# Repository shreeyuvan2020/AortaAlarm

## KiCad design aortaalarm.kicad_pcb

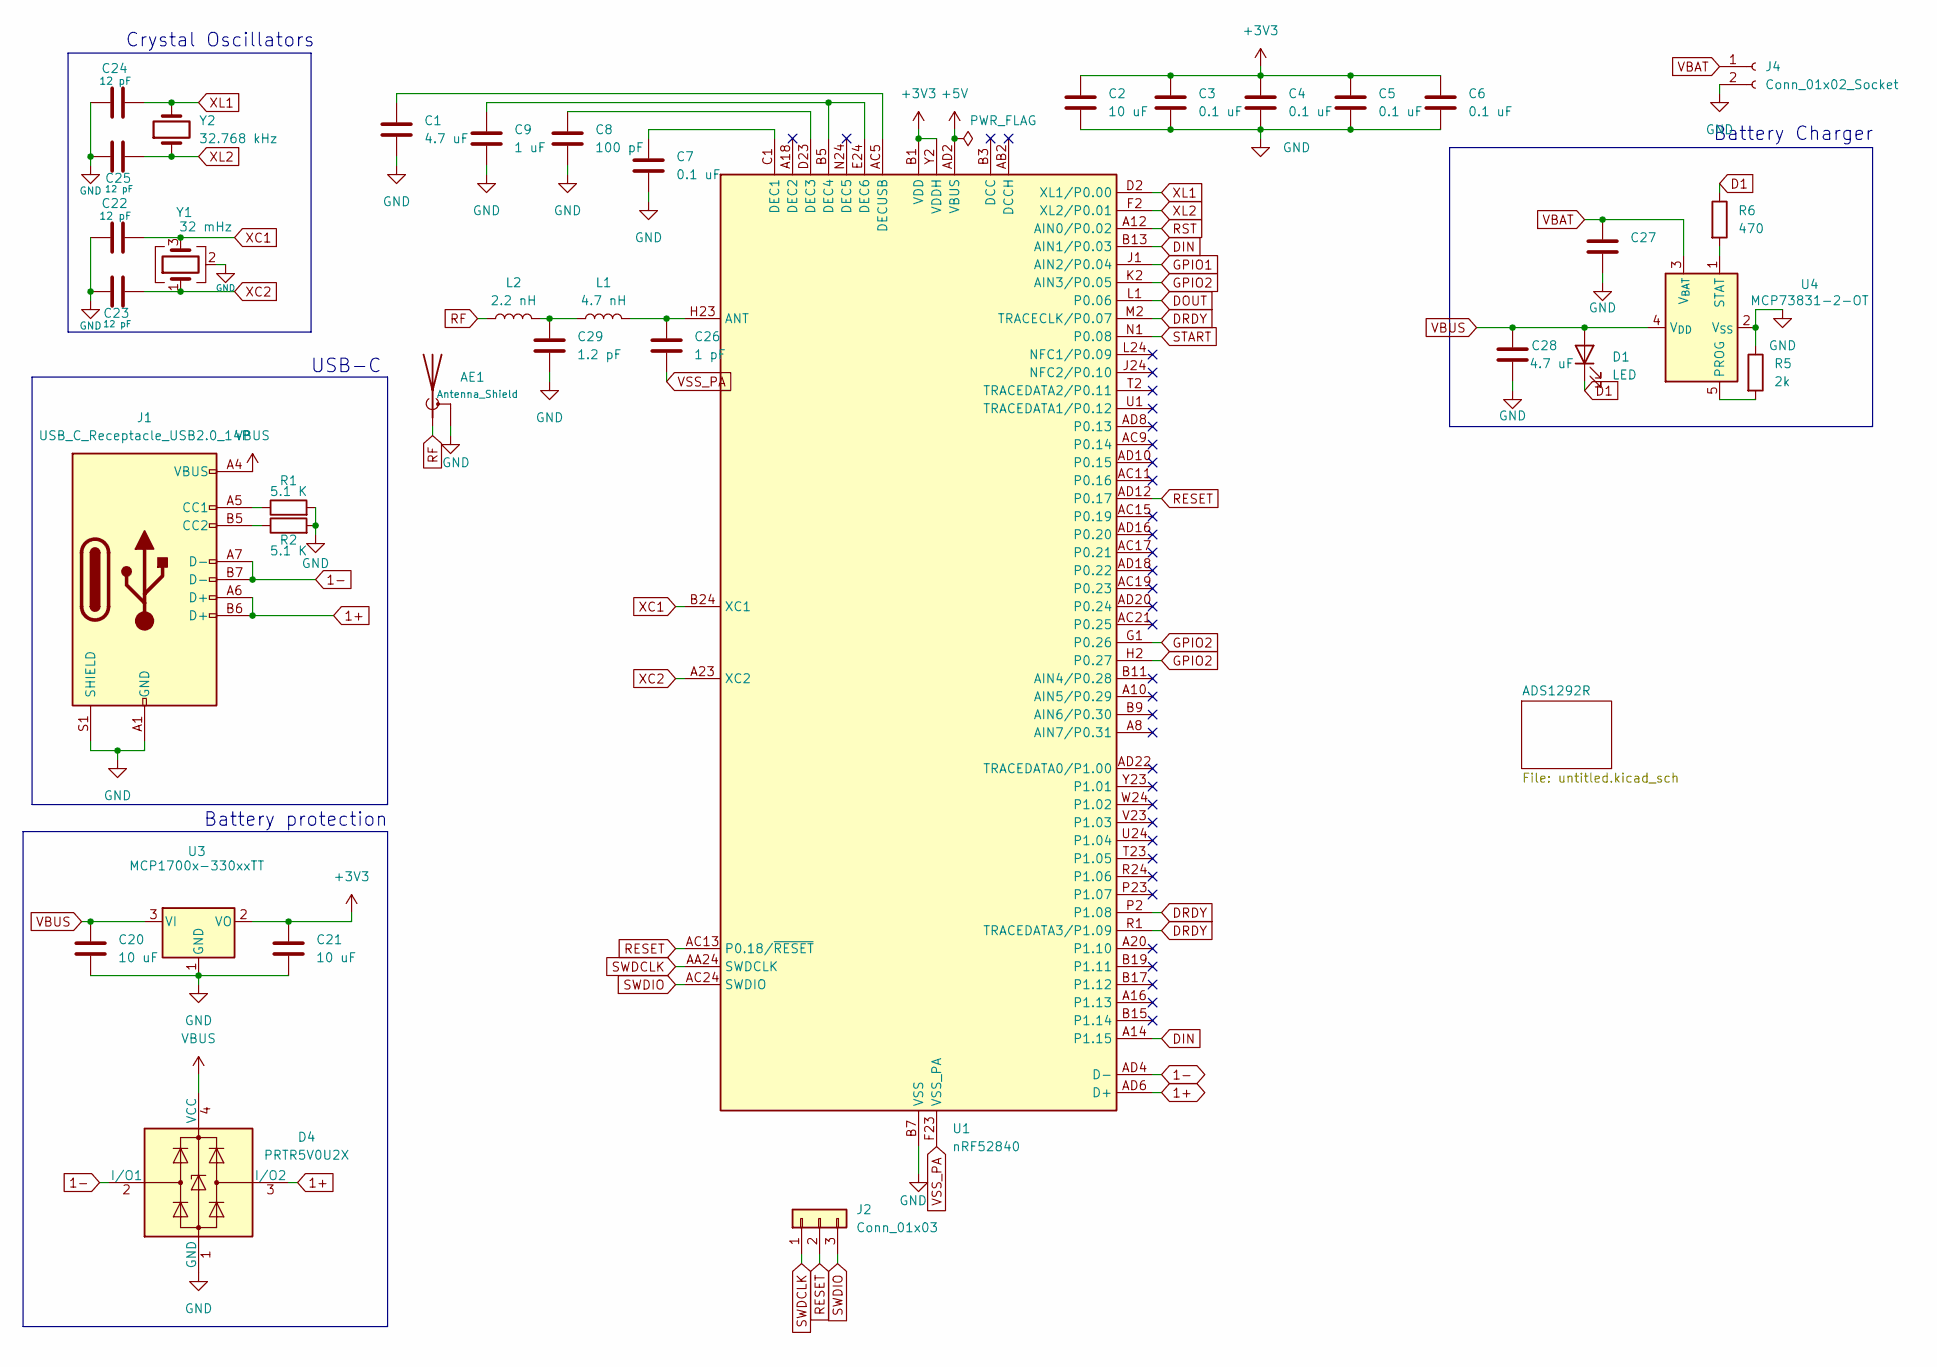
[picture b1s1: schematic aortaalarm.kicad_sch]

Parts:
AE1: Antenna_Shield; Texas_SWRA117D_2.4GHz_Right
C1, C27, C28: 4.7 uF; C_0603_1608Metric
C2, C20, C21: 10 uF; C_0603_1608Metric
C3, C4, C5, C6, C7: 0.1 uF; C_0402_1005Metric
C8: 100 pF; C_0402_1005Metric
C9: 1 uF; C_0402_1005Metric
C22, C23, C24, C25: 12 pF; C_0402_1005Metric
C26: 1 pF; C_0402_1005Metric
C29: 1.2 pF; C_0402_1005Metric
D1: LED; D_0805_2012Metric
D4: PRTR5V0U2X; SOT-143
J1: USB_C_Receptacle_USB2.0_14P; USB_C_Receptacle_HRO_TYPE-C-31-M-12
J2: Conn_01x03; PinHeader_1x03_P2.54mm_Vertical
J4: Conn_01x02_Socket; JST_PH_S2B-PH-K_1x02_P2.00mm_Horizontal
L1: 4.7 nH; L_0402_1005Metric
L2: 2.2 nH; L_0402_1005Metric
R1, R2: 5.1 K; R_0603_1608Metric
R5: 2k; R_0603_1608Metric
R6: 470; R_0603_1608Metric
U1: nRF52840; Nordic_AQFN-73-1EP_7x7mm_P0.5mm
U3: MCP1700x-330xxTT; SOT-23
U4: MCP73831-2-OT; SON50P200X300X100-9N
Y1: 32 mHz; Crystal_SMD_3225-4Pin_3.2x2.5mm
Y2: 32.768 kHz; Crystal_SMD_3215-2Pin_3.2x1.5mm

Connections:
1+: D4.3 (I/O2), J1.A6 (D+), J1.B6 (D+), U1.AD6 (D+)
1-: D4.2 (I/O1), J1.A7 (D-), J1.B7 (D-), U1.AD4 (D-)
+3V3: C2.1, C3.1, C4.1, C5.1, C6.1, C21.1, U1.A22 (VDD), U1.AD14 (VDD), U1.AD23 (VDD), U1.B1 (VDD), U1.W1 (VDD), U1.Y2 (VDDH), U3.2 (VO); also elsewhere on the board
+5V: U1.AD2 (VBUS)
D1: D1.1 (K), R6.1
DIN: U1.A14 (P1.15), U1.B13 (AIN1/P0.03); also elsewhere on the board
DOUT: U1.L1 (P0.06); also elsewhere on the board
DRDY: U1.M2 (TRACECLK/P0.07), U1.P2 (P1.08), U1.R1 (TRACEDATA3/P1.09); also elsewhere on the board
GND: AE1.2 (Shield), C1.2, C2.2, C3.2, C4.2, C5.2, C6.2, C7.2, C8.2, C9.2, C20.2, C21.2, C22.1, C23.1, C24.1, C25.1, C27.2, C28.2, C29.2, D4.1 (GND), J1.A1 (GND), J1.A12 (GND), J1.B1 (GND), J1.B12 (GND), J1.S1 (SHIELD), J4.2, R1.2, R2.2, R5.1, U1.B7 (VSS), U1.EP (VSS), U3.1 (GND), U4.2 (V_{SS}), Y1.2 (G), Y1.4 (G); also elsewhere on the board
GPIO1: U1.J1 (AIN2/P0.04); also elsewhere on the board
GPIO2: U1.G1 (P0.26), U1.H2 (P0.27), U1.K2 (AIN3/P0.05); also elsewhere on the board
unnamed: C29.1, L1.1, L2.2
unnamed: J1.A5 (CC1), R1.1
unnamed: J1.B5 (CC2), R2.1
unnamed: C26.1, L1.2, U1.H23 (ANT)
unnamed: C7.1, U1.C1 (DEC1)
unnamed: C8.1, U1.D23 (DEC3)
unnamed: C9.1, U1.B5 (DEC4), U1.E24 (DEC6)
unnamed: C1.1, U1.AC5 (DECUSB)
unnamed: R5.2, U4.5 (PROG)
unnamed: R6.2, U4.1 (STAT)
RESET: J2.2, U1.AC13 (P0.18/~RESET), U1.AD12 (P0.17)
RF: AE1.1 (A), L2.1
RST: U1.A12 (AIN0/P0.02); also elsewhere on the board
START: U1.N1 (P0.08); also elsewhere on the board
SWDCLK: J2.1, U1.AA24 (SWDCLK); also elsewhere on the board
SWDIO: J2.3, U1.AC24 (SWDIO)
VBAT: C27.1, J4.1, U4.3 (V_{BAT})
VBUS: C20.1, C28.1, D1.2 (A), D4.4 (VCC), J1.A4 (VBUS), J1.A9 (VBUS), J1.B4 (VBUS), J1.B9 (VBUS), U3.3 (VI), U4.4 (V_{DD})
VSS_PA: C26.2, U1.F23 (VSS_PA)
XC1: C22.2, U1.B24 (XC1), Y1.3
XC2: C23.2, U1.A23 (XC2), Y1.1
XL1: C24.2, U1.D2 (XL1/P0.00), Y2.2
XL2: C25.2, U1.F2 (XL2/P0.01), Y2.1

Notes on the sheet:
Battery protection
USB-C
Crystal Oscillators
Battery Charger

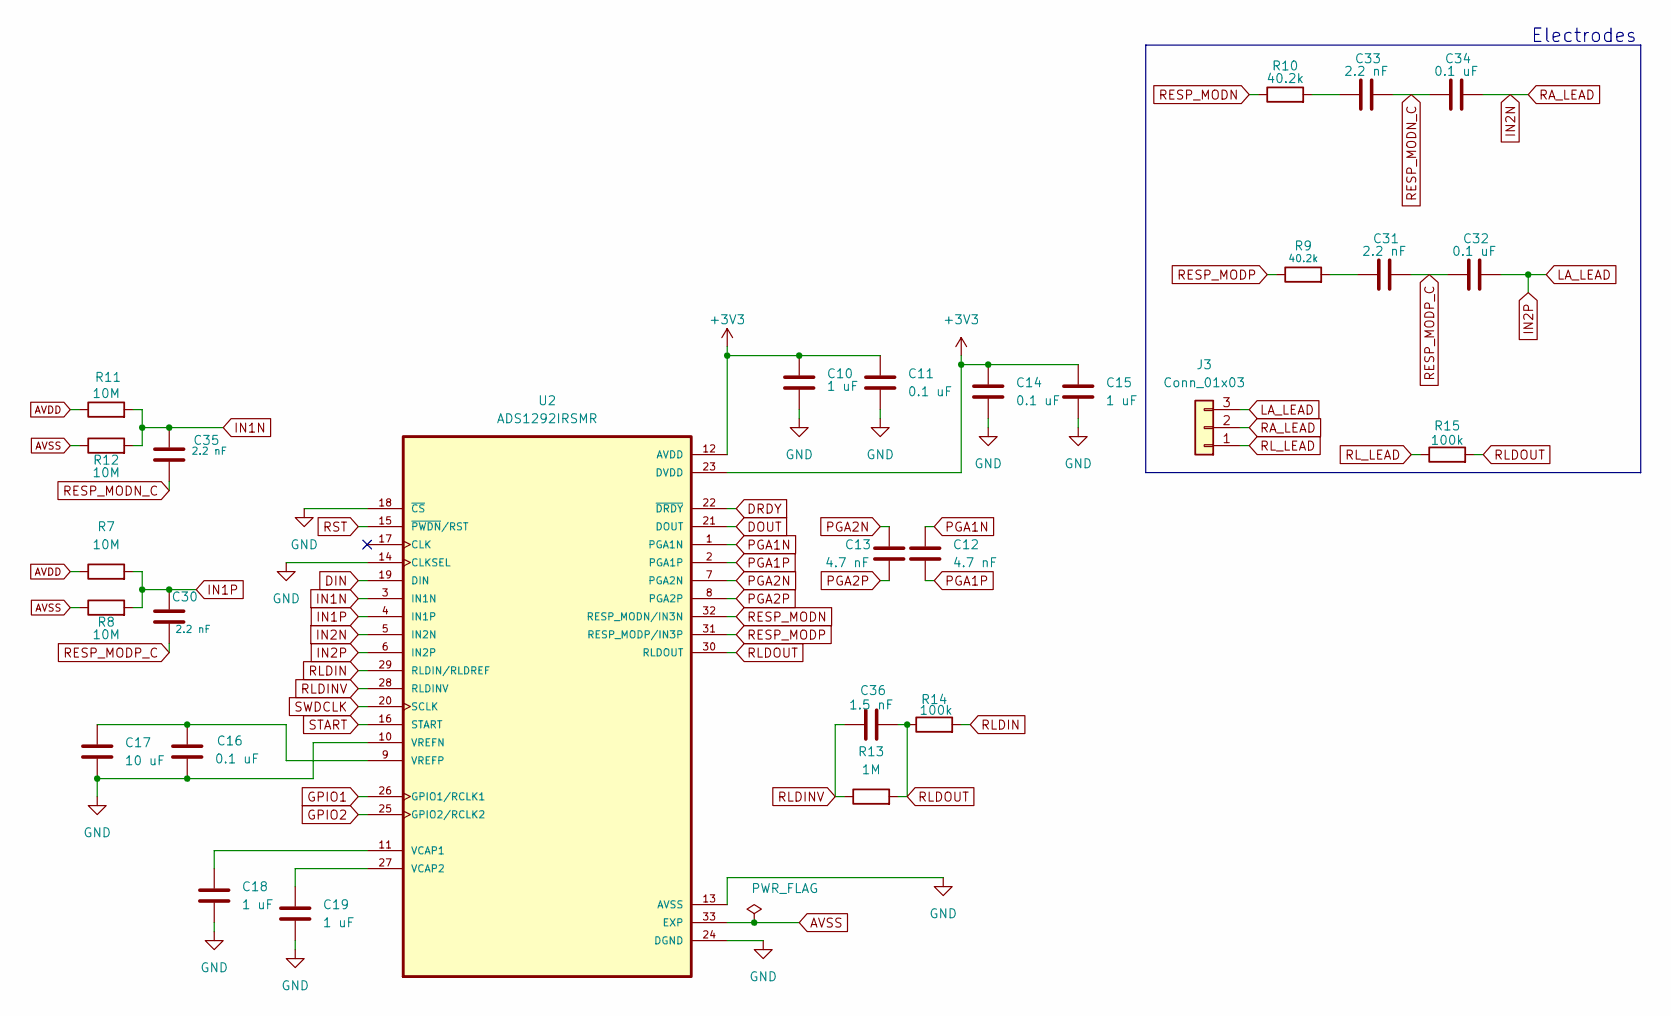
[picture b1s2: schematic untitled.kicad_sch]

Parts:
C10, C15, C18, C19: 1 uF; C_0402_1005Metric
C11, C14, C16, C32, C34: 0.1 uF; C_0402_1005Metric
C12, C13: 4.7 nF; C_0402_1005Metric
C17: 10 uF; C_0603_1608Metric
C30, C31, C33, C35: 2.2 nF; C_0402_1005Metric
C36: 1.5 nF; C_0402_1005Metric
J3: Conn_01x03; PinSocket_1x03_P2.54mm_Vertical
R7, R8, R11, R12: 10M; R_0603_1608Metric
R9, R10: 40.2k; R_0603_1608Metric
R13: 1M; R_0603_1608Metric
R14, R15: 100k; R_0603_1608Metric
U2: ADS1292IRSMR; QFN40P400X400X100-33N

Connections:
+3V3: C10.1, C11.1, C14.1, C15.1, U2.12 (AVDD), U2.23 (DVDD); also elsewhere on the board
AVDD: R7.1, R11.1
AVSS: R8.1, R12.1, U2.33 (EXP), U2.33_1 (EXP), U2.33_2 (EXP), U2.33_3 (EXP), U2.33_4 (EXP), U2.33_5 (EXP)
DIN: U2.19 (DIN); also elsewhere on the board
DOUT: U2.21 (DOUT); also elsewhere on the board
DRDY: U2.22 (~DRDY); also elsewhere on the board
GND: C10.2, C11.2, C14.2, C15.2, C16.2, C17.2, C18.2, C19.2, U2.10 (VREFN), U2.13 (AVSS), U2.14 (CLKSEL), U2.18 (~CS), U2.24 (DGND); also elsewhere on the board
GPIO1: U2.26 (GPIO1/RCLK1); also elsewhere on the board
GPIO2: U2.25 (GPIO2/RCLK2); also elsewhere on the board
IN1N: C35.1, R11.2, R12.2, U2.3 (IN1N)
IN1P: C30.1, R7.2, R8.2, U2.4 (IN1P)
IN2N: C34.1, J3.2, U2.5 (IN2N)
IN2P: C32.1, J3.3, U2.6 (IN2P)
unnamed: C31.2, R9.2
unnamed: C33.2, R10.2
unnamed: C18.1, U2.11 (VCAP1)
unnamed: C19.1, U2.27 (VCAP2)
unnamed: C16.1, C17.1, U2.9 (VREFP)
PGA1N: C12.1, U2.1 (PGA1N)
PGA1P: C12.2, U2.2 (PGA1P)
PGA2N: C13.1, U2.7 (PGA2N)
PGA2P: C13.2, U2.8 (PGA2P)
RESP_MODN: R10.1, U2.32 (RESP_MODN/IN3N)
RESP_MODN_C: C33.1, C34.2, C35.2
RESP_MODP: R9.1, U2.31 (RESP_MODP/IN3P)
RESP_MODP_C: C30.2, C31.1, C32.2
RLDIN: R14.2, U2.29 (RLDIN/RLDREF)
RLDINV: C36.1, R13.1, U2.28 (RLDINV)
RLDOUT: C36.2, R13.2, R14.1, R15.2, U2.30 (RLDOUT)
RL_LEAD: J3.1, R15.1
RST: U2.15 (~PWDN/RST); also elsewhere on the board
START: U2.16 (START); also elsewhere on the board
SWDCLK: U2.20 (SCLK); also elsewhere on the board

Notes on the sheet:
Electrodes

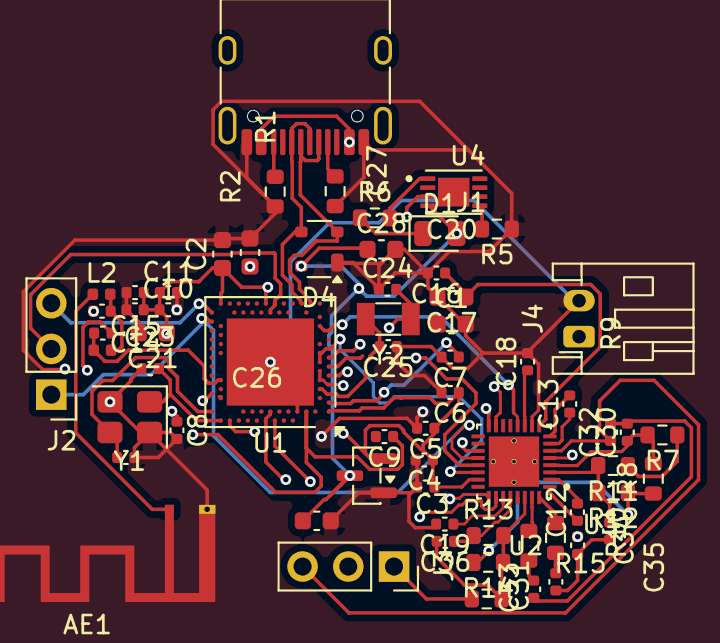
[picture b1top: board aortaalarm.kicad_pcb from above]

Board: 6 copper layers, 64 parts (0 on the bottom side), 56 nets.

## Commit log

2026-06-21 dajhf
2026-06-21 add readme
2026-06-21 add more stuff
2026-06-21 add mor stuff
